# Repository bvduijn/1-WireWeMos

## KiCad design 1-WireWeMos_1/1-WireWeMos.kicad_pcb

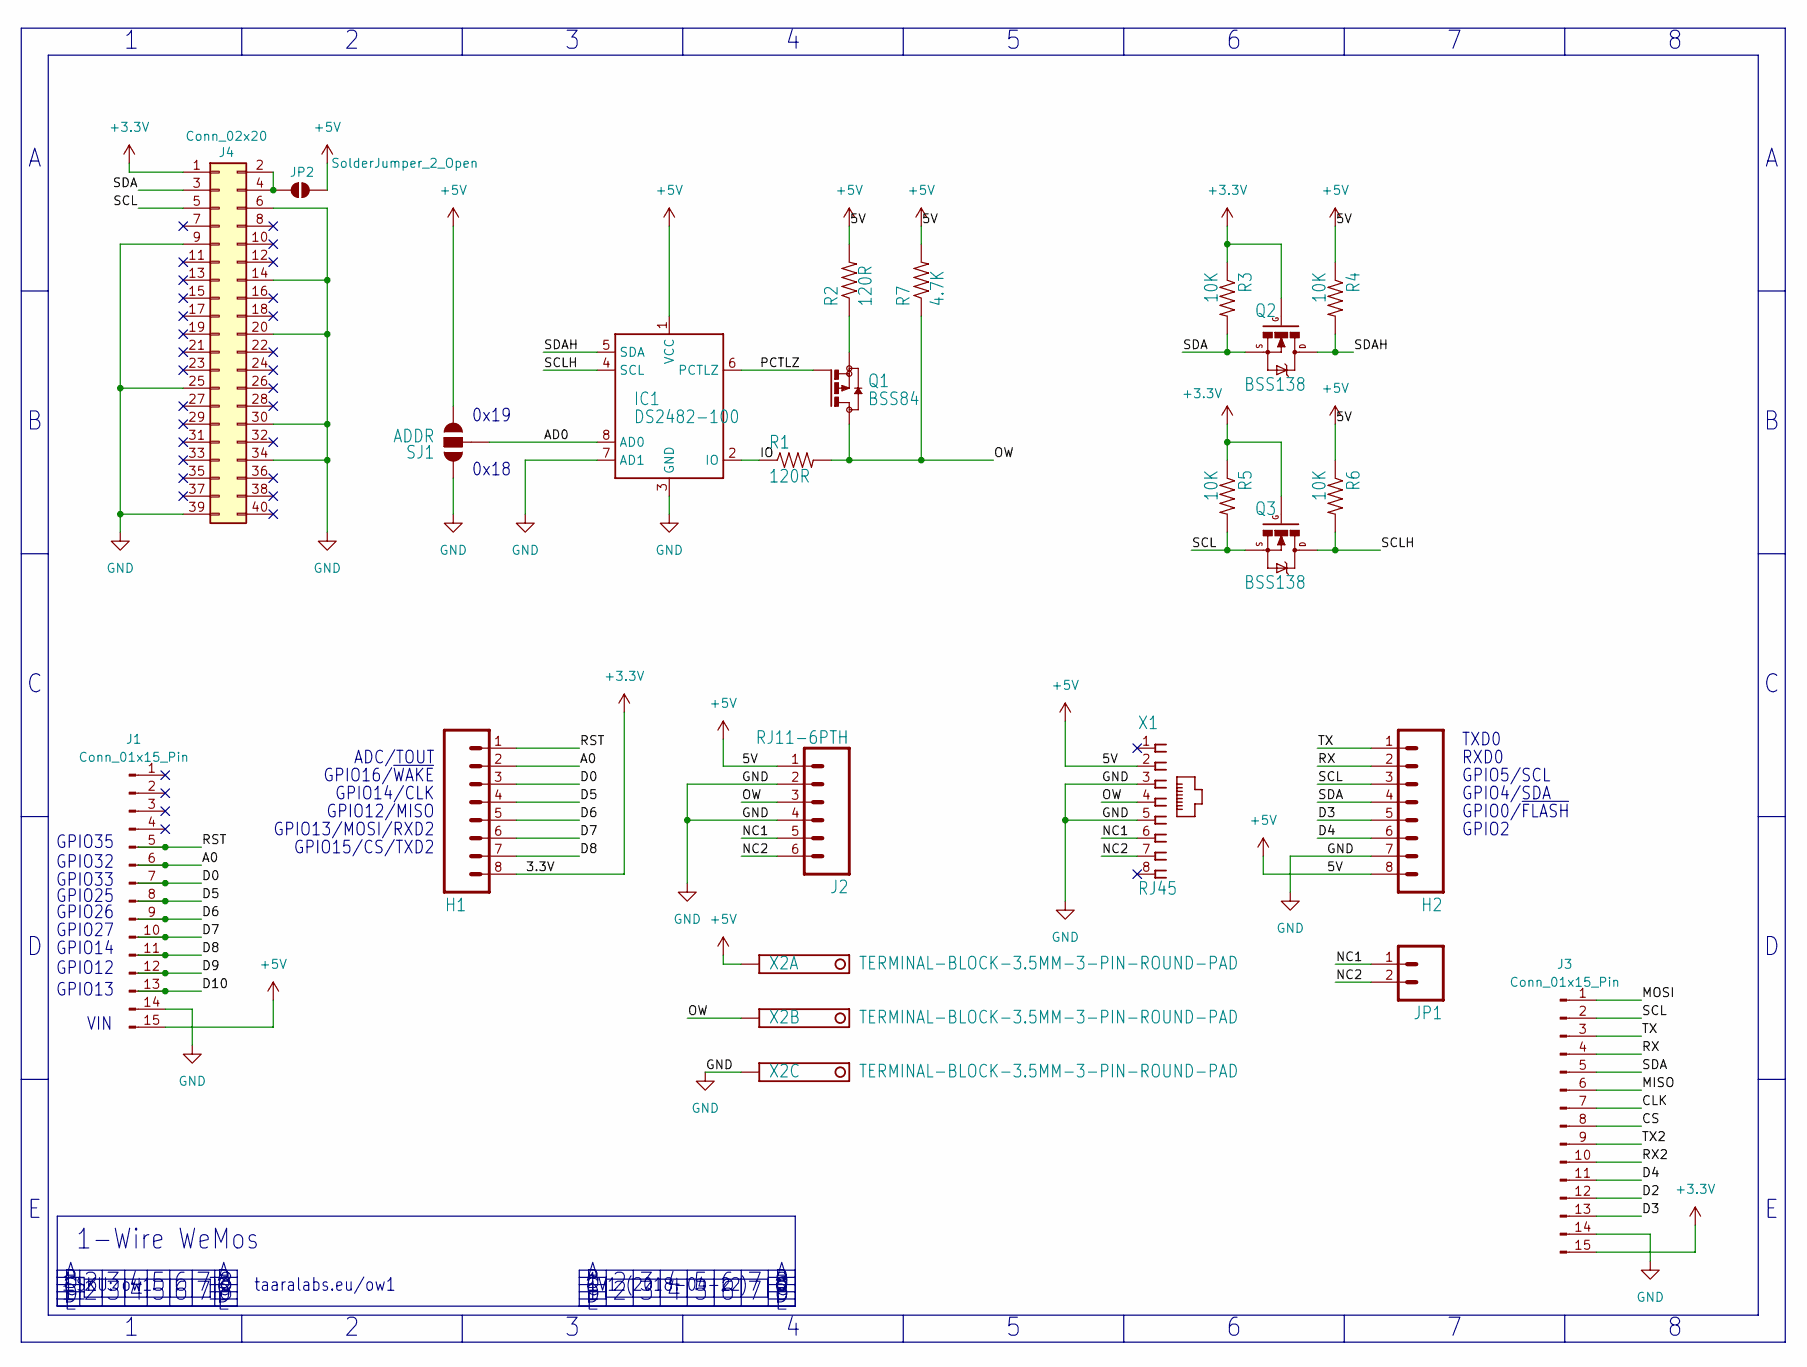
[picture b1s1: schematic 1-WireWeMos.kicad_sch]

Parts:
H1, H2: M08; 1X08
IC1: DS2482-100; SO08
J1, J3: Conn_01x15_Pin; PinHeader_1x15_P2.54mm_Vertical
J2: RJ11-6PTH; RJ11-6
J4: Conn_02x20; PinSocket_2x19_P2.54mm_Vertical
JP1: M02PTH; 1X02
JP2: SolderJumper_2_Open; SolderJumper-2_P1.3mm_Open_Pad1.0x1.5mm
Q1: BSS84; SOT23
Q2, Q3: BSS138; SOT23-3
R1, R2: 120R; 0603-RES
R3, R4, R5, R6: 10K; 0603-RES
R7: 4.7K; 0603-RES
SJ1: ADDR; SJ_3_PASTE1&2
X1: RJ45; RJ45-NO-SHIELD
X2: TERMINAL-BLOCK-3.5MM-3-PIN-ROUND-PAD; TERMINAL-BLOCK-3-PIN-3.5MM-ROUND-PAD

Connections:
+3.3V: H1.8, J3.15, J4.1, Q2.1 (G), Q3.1 (G), R3.1, R5.1
+5V: H2.8, IC1.1 (VCC), J1.15, J2.1, JP2.2 (B), R2.2, R4.1, R6.1, R7.2, SJ1.3, X1.2, X2.1 (K)
/A0: H1.2, J1.6
/AD0: IC1.8 (AD0), SJ1.2
/CLK: J3.7
/CS: J3.8
/D0: H1.3, J1.7
/D2: J3.12
/D3: H2.5, J3.13
/D4: H2.6, J3.11
/D5: H1.4, J1.8
/D6: H1.5, J1.9
/D7: H1.6, J1.10
/D8: H1.7, J1.11
/D9: J1.12
/D10: J1.13
/IO: IC1.2 (IO), R1.1
/MISO: J3.6
/MOSI: J3.1
/NC1: J2.5, JP1.1, X1.6
/NC2: J2.6, JP1.2, X1.7
/OW: J2.3, Q1.3 (D), R1.2, R7.1, X1.4, X2.2 (K)
/PCTLZ: IC1.6 (PCTLZ), Q1.1 (G)
/RST: H1.1, J1.5
/RX: H2.2, J3.4
/RX2: J3.10
/SCL: H2.3, J3.2, J4.5, Q3.2 (S), R5.2
/SCLH: IC1.4 (SCL), Q3.3 (D), R6.2
/SDA: H2.4, J3.5, J4.3, Q2.2 (S), R3.2
/SDAH: IC1.5 (SDA), Q2.3 (D), R4.2
/TX: H2.1, J3.3
/TX2: J3.9
GND: H2.7, IC1.3 (GND), IC1.7 (AD1), J1.14, J2.2, J2.4, J3.14, J4.6, J4.9, J4.14, J4.20, J4.25, J4.30, J4.34, J4.39, SJ1.1, X1.3, X1.5, X2.3 (K)
unnamed: J4.2, J4.4, JP2.1 (A)
unnamed: Q1.2 (S), R2.1

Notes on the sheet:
GPIO13/MOSI/RXD2
ADC/TOUT
GPIO25
GPIO16/~{WAKE}
GPIO2
GPIO15/CS/TXD2
GPIO33
taaralabs.eu/ow1
SKU: ow1
GPIO0/~{FLASH}
GPIO27
0x18
GPIO35
V1 (2018-04-22)
1-Wire WeMos
GPIO4/SDA
GPIO5/SCL
GPIO14/CLK
TXD0
GPIO12
GPIO32
0x19
VIN
GPIO26
GPIO12/MISO
GPIO14
GPIO13
RXD0

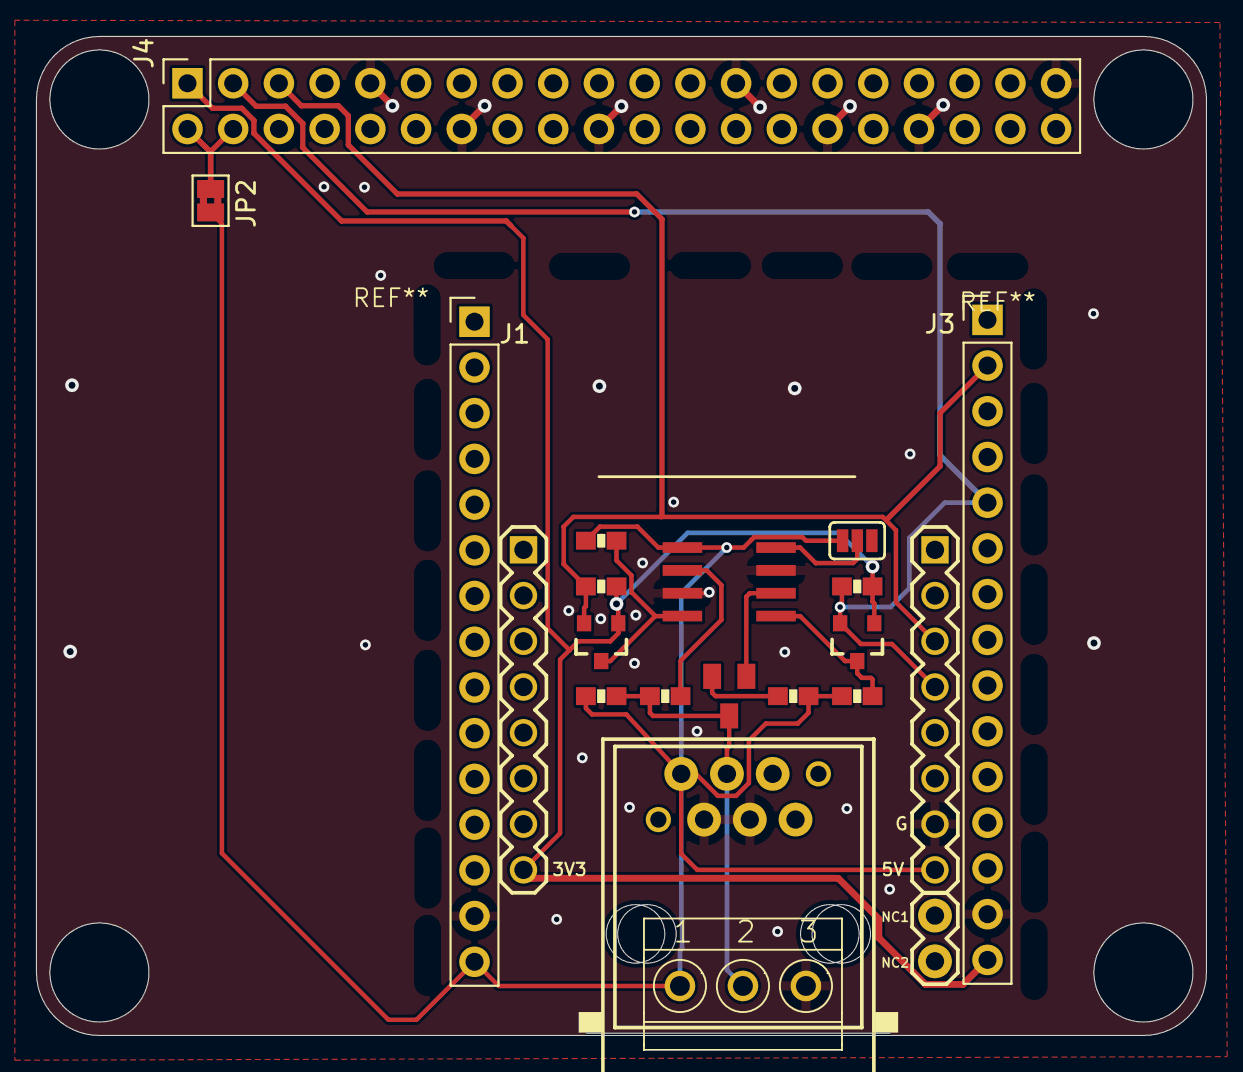
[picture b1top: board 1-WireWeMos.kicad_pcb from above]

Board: 2 copper layers, 65.0 x 55.5 mm, 22 parts (0 on the bottom side), 26 nets.

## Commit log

2025-05-10 add rpi hat layout
